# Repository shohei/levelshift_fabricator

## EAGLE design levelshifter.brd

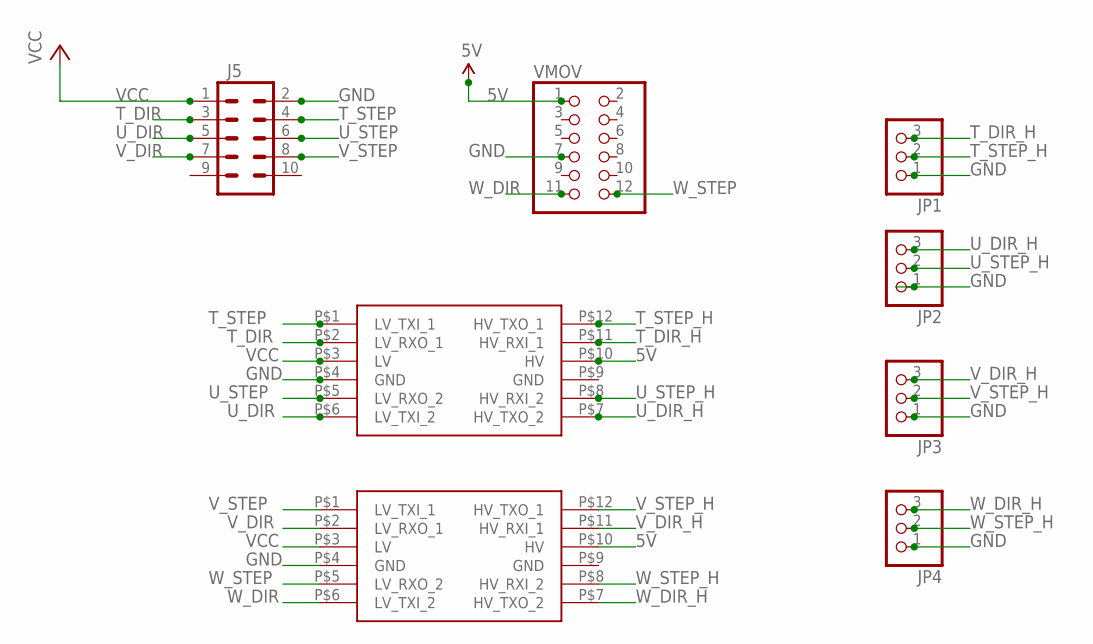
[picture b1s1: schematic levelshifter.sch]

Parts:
CP, CP1: LOGIC_LEVEL_CONVERTER
J5: M05X2PTH; AVR_ICSP
JP1, JP2, JP3, JP4: PINHD-1X3; 1X03
VMOV: PINHD-2X6; 2X06

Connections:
5V: CP.P$10 (HV), CP1.P$10 (HV), VMOV.1
GND: CP.P$4 (GND), CP1.P$4 (GND), J5.2, JP1.1, JP2.1, JP3.1, JP4.1, VMOV.7
T_DIR: CP.P$2 (LV_RXO_1), J5.3
T_DIR_H: CP.P$11 (HV_RXI_1), JP1.3
T_STEP: CP.P$1 (LV_TXI_1), J5.4
T_STEP_H: CP.P$12 (HV_TXO_1), JP1.2
U_DIR: CP.P$6 (LV_TXI_2), J5.5
U_DIR_H: CP.P$7 (HV_TXO_2), JP2.3
U_STEP: CP.P$5 (LV_RXO_2), J5.6
U_STEP_H: CP.P$8 (HV_RXI_2), JP2.2
VCC: CP.P$3 (LV), CP1.P$3 (LV), J5.1
V_DIR: CP1.P$2 (LV_RXO_1), J5.7
V_DIR_H: CP1.P$11 (HV_RXI_1), JP3.3
V_STEP: CP1.P$1 (LV_TXI_1), J5.8
V_STEP_H: CP1.P$12 (HV_TXO_1), JP3.2
W_DIR: CP1.P$6 (LV_TXI_2), VMOV.11
W_DIR_H: CP1.P$7 (HV_TXO_2), JP4.3
W_STEP: CP1.P$5 (LV_RXO_2), VMOV.12
W_STEP_H: CP1.P$8 (HV_RXI_2), JP4.2

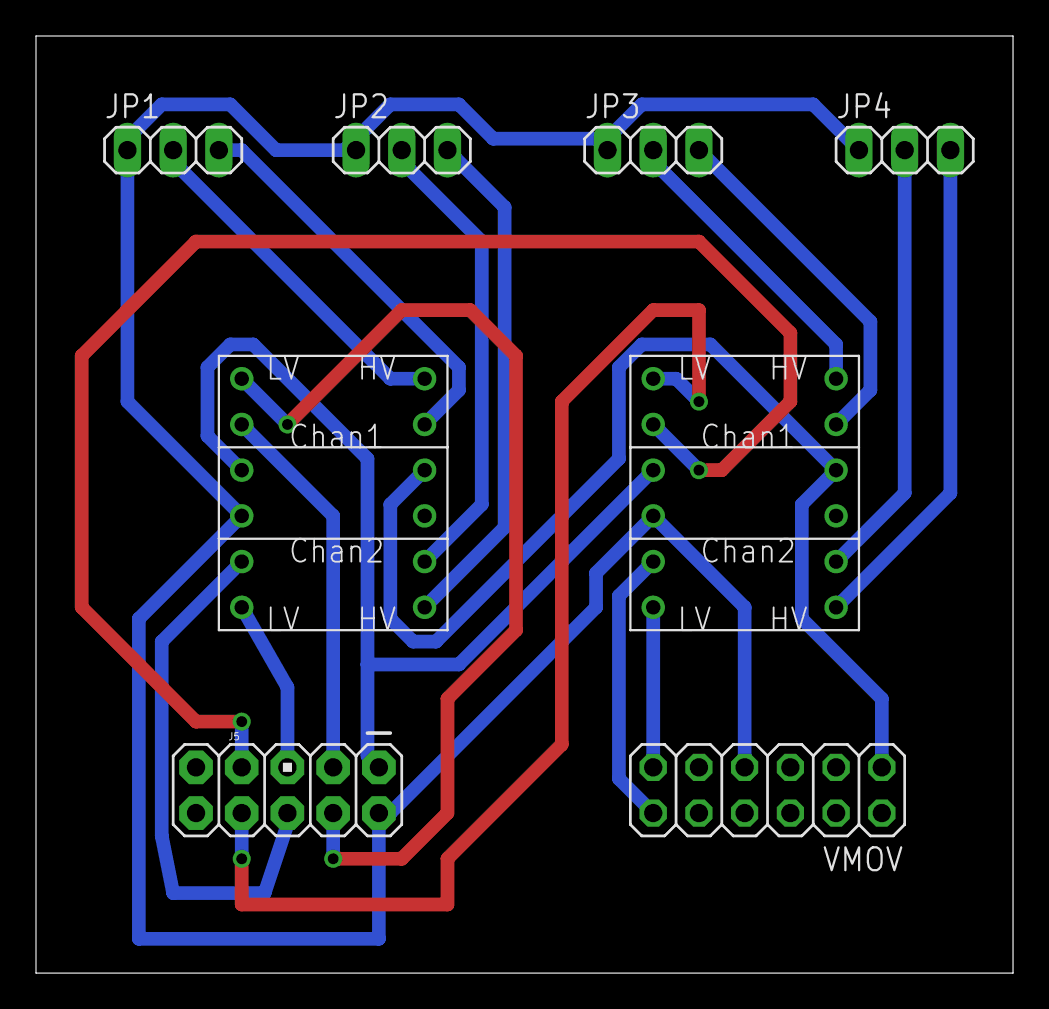
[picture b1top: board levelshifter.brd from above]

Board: 2 copper layers, 54.3 x 52.1 mm, 8 parts (0 on the bottom side), 19 nets.

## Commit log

2016-11-24 add image

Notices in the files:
parts and their libraries:
SparkFun-Boards: Licensing: Creative Commons ShareAlike 4.0 International - https://creativecommons.org/licenses/by-sa/4.0
